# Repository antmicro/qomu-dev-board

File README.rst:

======================
Qomu Development Board
======================

.. figure:: img/qomu-board.png

Overview
========

This repository contains open hardware design files for the Qomu development board based on the QuickLogic `EOS S3 Sensor Processing Platform <https://www.quicklogic.com/products/eos-s3/>`_.
The design files were created by `Antmicro <https://www.antmicro.com>`_ in cooperation with `QuickLogic <https://www.quicklogic.com/>`_.
The board is small enough to fit into a USB socket.
This allows the user to explore functionalities of the EOS S3 platform on the go without cables or taking up space on your desk.
The board has an additional break-away part with debug connectors that speeds up initial bringup and software development.

Key features
============

* EOS S3 Sensor Processing Platform
* 16Mbit of external flash memory
* Accelerometer
* User RGB LED
* Capacitive touch pads
* Powered with 5.0VDC from USB port
* USB data signals tied to programmable logic

Layout and dimensions
=====================

.. figure:: img/qomu-layout.png

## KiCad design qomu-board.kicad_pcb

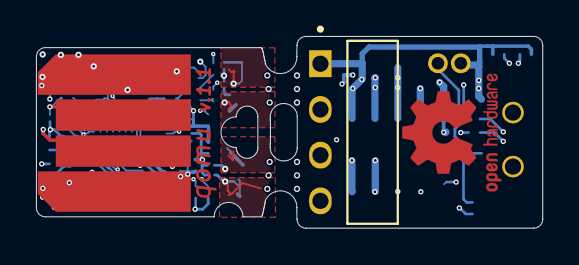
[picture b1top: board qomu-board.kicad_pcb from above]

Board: 6 copper layers, 28.1 x 10.6 mm, 69 parts (0 on the bottom side), 45 nets.

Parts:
C1, C2, C7, C9, C15, C16: 2u2/10V; C_0201_0603Metric
C3, C4, C5, C6, C8, C10, C12: 100n; C_0201_0603Metric
C13, C14: 8p; C_0201_0603Metric
D1, D2, D3, D4, D6, D7: D5V0L1B2LP3-7; X1-DFN1006-2
D5: VCUT05E1-SD0; X1-DFN1006-2
D8: SD05C.TCT; SOD-323-SD05
IC1: EOS-S3; 42-WLCSP
J1: FTSH-105-01-L-DV-K; PinHeader_2x5_P1.27_SMD
J2: 825437-4; TE_825437-4
J3: MC-HVT1-S02-G; PinHeader_1x2_P1.27mm_Drill.7mm_with_622002115121_plug
N1: oshw_logo; OSHW-Logo2_7.3x6mm_Copper_Mask
N2: antmicro_logo; antmicro-logo_midlayer_4mm
N3: ql_logo; Ql_logo_mid_9mm
Q1, Q2, Q3: RV1C002UN; VML0806
R1, R2, R5, R6, R13, R15: 10k; R_0201_0603Metric
R3, R4, R8: 4k7; R_0201_0603Metric
R7, R10: 0R; R_0201_0603Metric
R9: 1k5; R_0201_0603Metric
R11, R12: 22R; R_0201_0603Metric
R16, R17: 100R; R_0201_0603Metric
R18: 220R; R_0201_0603Metric
S1: MSS3-V-T_R; Switch_Slide_MSS3
SW2: Captouch Pads; captouch-edge
TP1, TP2, TP3, TP9, TP10: TP_SMD_0_75MM; Testpoint_smd_0_75_0_6mm
TP4, TP5, TP6, TP7, TP8: TP_SMD_0_75MM; Testpoint_smd_0_75mm
U1, U2: MIC5504-3.3YMT; Texas_X2SON-4_1x1mm_P0.65mm
U4: GD25Q16CEIGR
U5: MC3635
U9: USB-B; USB-PCB
U10: UHD1110-FKA; LED-RGB-5DS-UHD1110-FKA
XTAL1: ECS-_327-12_5-1210-TR; XTAL_ECS-.327-12.5-1210-TR

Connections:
+3V3: C3.1, C4.2, C5.2, C6.1, C8.1, C9.1, C12.1, D8.K, IC1.B3, IC1.C2, IC1.C6, J1.1, J2.1, J3.1, R1.2, R3.2, R4.2, R8.2, R13.2, R15.2, S1.1, U2.1, U4.3, U4.7, U4.8, U5.6, U5.7, U5.9, U10.4
+VBUS: C1.1, C2.1, D5.1, U1.3, U1.4, U2.3, U2.4, U9.1
/ACC_INT: IC1.C7, R8.1, U5.5
/C1: IC1.C1, R6.1, TP3.1
/E1: IC1.E1, TP2.1
/F2: IC1.F2, TP10.1
/I2C_SCL: IC1.A7, R4.1, U5.10
/I2C_SDA: IC1.B7, R3.1, U5.2
/LED_B: IC1.F4, Q3.1
/LED_BK: R16.2, U10.1
/LED_G: IC1.A5, Q2.1, R2.1
/LED_GK: R17.2, U10.2
/LED_R: IC1.D2, Q1.1
/LED_RK: R18.2, U10.3
/PU_CTRL_USBP: IC1.E2, R9.1
/RST_N: IC1.F1, J1.10, R1.1, TP1.1
/R_USB_N: IC1.F3, R11.1
/R_USB_P: IC1.E4, R12.1
/SPI_MISO: IC1.F5, TP7.1, U4.2
/SPI_MOSI: IC1.E6, TP4.1, U4.5
/SPI_SCLK: IC1.D5, TP6.1, U4.6
/SPI_SS: IC1.F6, TP5.1, U4.1
/SWD_CLK: IC1.A4, J1.4, R13.1
/SWD_IO: IC1.B4, J1.2, R15.1
/TOUCH_1: D4.1, IC1.B5, SW2.1
/TOUCH_2: D2.1, IC1.D3, SW2.2
/TOUCH_3: D3.1, IC1.D7, SW2.3
/TOUCH_4: D1.1, IC1.E3, SW2.4
/UART_RX: IC1.F7, J2.3, R10.1
/UART_TX: IC1.E7, J2.2, R7.1
/USB_N: D7.1, R11.2, U9.2
/USB_P: D6.1, R9.2, R12.2, U9.3
/VCCIOB: C7.2, C10.1, IC1.D6, U1.1
/VDD1: C16.2, IC1.A2
/VDD2: C15.2, IC1.A3
GND: C1.2, C2.2, C3.2, C4.1, C5.1, C6.2, C7.1, C8.2, C9.2, C10.2, C12.2, C13.2, C14.2, C15.1, C16.1, D1.2, D2.2, D3.2, D4.2, D5.2, D6.2, D7.2, D8.A, IC1.C3, IC1.C4, IC1.C5, IC1.D4, IC1.E5, J1.3, J1.5, J1.9, J2.4, Q1.2, Q2.2, Q3.2, R2.2, R5.1, TP8.1, TP9.1, U1.2, U1.5, U2.2, U2.5, U4.4, U5.1, U5.4, U5.8, U9.4
unnamed: C13.1, IC1.B1, XTAL1.1
unnamed: C14.1, IC1.A1, XTAL1.2
unnamed: IC1.B6, R5.2
unnamed: J1.6, R7.2
unnamed: J1.8, R10.2
unnamed: J3.2, R6.2, S1.2
unnamed: Q1.3, R18.1
unnamed: Q2.3, R17.1
unnamed: Q3.3, R16.1

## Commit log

2019-11-08 Initial commit- PCB design files for Fomu (production) taken from https://github.com/im-tomu/fomu-hardware commit 07383f38da9d5a36aa6105ee2a01cb04b6fe3e73
2019-11-25 Updated project name
2019-11-25 Schematic/PCB cleanup
2020-02-13 Added EOS-S3 and flash memory to schematics
2020-02-13 Added accelerometer, changed flash memory
2020-02-13 Connected U4 and U5 to EOS S3
2020-02-13 Added plastic case outline to PCB, defined initial component placement
2020-02-13 Fixed missing library components, fixed MC3635 footprint
2020-02-13 Added OSHW logotypes
2020-02-13 Updated component placement
2020-02-13 Added README
2020-02-13 Connected missing nets, schematic cleanup
2020-02-13 Fixed USB_D_P pull-up connection, tied U5 CS pin to VDDIO, added some remarks on schematics
2020-02-13 Cleanup
2020-02-13 Updated naming
2020-02-13 Updated PDF schematics
2020-02-13 Add PDF schematics
2020-02-13 Updated MPN for LDO
2020-02-13 Cleanup, updated .gitignore
2020-02-13 Added single LDO as power supply, cleanup
2020-02-13 Minor changes
2020-02-13 Added notes regarding power consumption
2020-02-13 Moved all library elements to lib directory, migrated all components to this library
2020-02-13 Added additional LDO and bypass capacitors for EOS S3
2020-02-13 Added schematics PDF
2020-02-13 Connected VCCIOA and VCCIOB to proper rails, added power port symbols, added pull-up resistor for IMU interrupt, added bootstrap resistors
2020-02-13 Added TBDs
2020-02-13 Minor updates to BOM
2020-02-13 Update PDF schematics
2020-02-13 Added BOM
2020-02-13 Added headers for debug and programming
2020-02-13 Added LED driving transistors
2020-02-13 Initial component placement
2020-02-13 Component layout condensed to fit plastic enclosure
2020-02-13 Library cleanup, added MPNs for all components
2020-02-13 Corrected Mb/Mbit notation in README
2020-02-13 Board shape altered: added debug expansion part
2020-02-13 BOM updated
2020-02-13 Updated 3D vis
2020-02-13 Removed DBG_SS signal
2020-02-13 Small fixes in BOM
2020-02-13 Connected touch signals to IC1
2020-02-13 Removed R6 and R7
2020-02-13 Updated PDF with schematic, updated BOM
2020-02-13 PCB routing
2020-02-13 Added oscillator, updated component placement
2020-02-13 Added testpoints to PCB
2020-02-13 TOUCHx connection changed
2020-02-13 ECX-1210 3d model update
2020-02-13 Added GP testpoints, routing
2020-02-13 Routing of power planes
2020-02-13 USB connector position fix
2020-02-13 Removed soldermask from TOUCHx pads
2020-02-13 Edited tech notes on PCB
2020-02-13 Changed jumper pitch to 1.27mm, added SMD switch
2020-02-13 Routing completed
2020-02-13 Resolved DRC errors
2020-02-13 Updated BOM and 3DVis
2020-02-13 Updated 3D models
2020-02-13 R7,R10,S1 options restored. Library link fixed
2020-02-13 Pin swaps implemented on PCB
2020-02-13 Fixed footprints for J3 and D8
2020-02-13 Testpoint on F2 added
2020-02-13 Added logotypes, updated copper ballance
2020-02-13 Updated schematic notes, re-generated PDF
2020-02-13 Added Gerber files, updated schematic PDF
2020-02-13 Added optional jumpers to enable UART TX/RX on unassigned J1 pins
2020-02-13 Touch_2 and LEDG swapped on schematic. USB_P and Touch_4 (FBIO_31) swapped on schematic
2020-02-13 Updated datasheet link for EOS
2020-02-13 Updated BOM
2020-02-13 Updated library
2020-02-13 Updated directory structure
2020-02-13 Updated gerber files, updated schematic PDF
2020-02-13 Updated descriptions on silk overlay
2020-02-13 Updated signage
2020-02-13 README: Added mention about debug break-away part
2020-02-13 Review README
2020-02-13 Updated schematic PDF
2020-02-13 Added documentation for manufacturing prototypes in rev. 1.0
2020-02-13 PCB adopted to narrower version of GD25Q16, revision changed to 1.1
2020-02-13 Updated footprint of GD25Q16CEIGR flash memory
2020-02-13 Added production files for rev. 1.1
2020-03-06 Updated pin 1 marking on RGB LED
2020-03-06 Added bulk capacitors to EOS internal VDD1/1. Removed C11
2020-03-06 Updated revision markings
2020-03-06 U4 designator is now hidden
2020-03-06 Updated manufacturing documentation
2020-03-06 Updated PCB documentation
2020-03-28 Minor review of README
2020-04-01 LED_G reconnected to FBIO9
2020-04-01 Updated production documentation
2020-04-01 Add 3D STL model
2020-05-22 Remove redundant pnp files
2021-06-24 Notes added by 'git notes add'

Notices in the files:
qomu-board.kicad_pcb:
License: CC-BY-SA 4.0 or TAPR
